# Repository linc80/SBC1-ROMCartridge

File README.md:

# SBC1-ROMCartridge
Contains the L80RomCartridge and L80RomCart-Adapter, needed to use the ROMSLOT header on a LiNC80 SBC1

The current version references libraries not included in the repository. There is a current TODO to change this over to using library files in the working project path, and verify compatibility with KiCad 5.

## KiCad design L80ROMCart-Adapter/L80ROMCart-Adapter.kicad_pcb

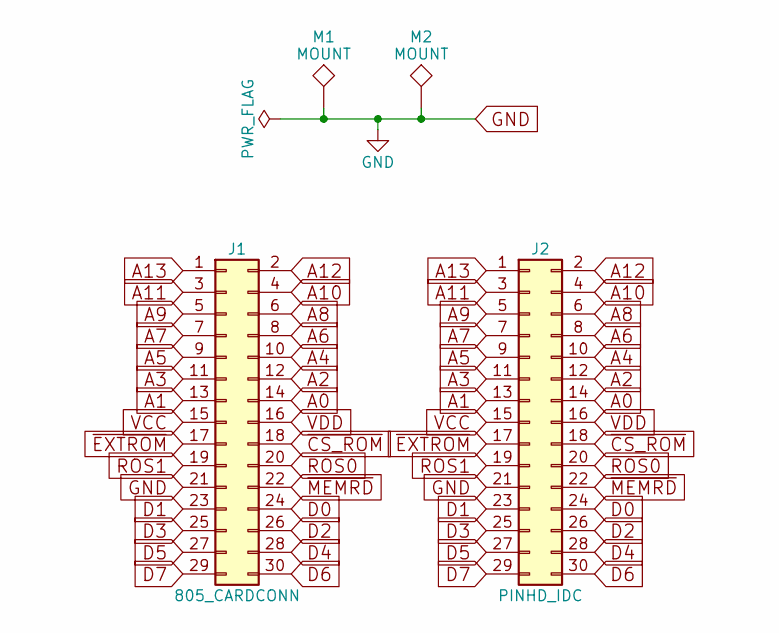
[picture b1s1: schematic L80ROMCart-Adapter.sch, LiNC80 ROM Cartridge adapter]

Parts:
J1: 805_CARDCONN; 805-connector-30pin
J2: PINHD_IDC; Pin_Header_Straight_2x15_Pitch2.54mm
M1, M2: MOUNT; MountingHole_3.5mm_Pad

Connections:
A0: J1.14, J2.14
A1: J1.13, J2.13
A2: J1.12, J2.12
A3: J1.11, J2.11
A4: J1.10, J2.10
A5: J1.9, J2.9
A6: J1.8, J2.8
A7: J1.7, J2.7
A8: J1.6, J2.6
A9: J1.5, J2.5
A10: J1.4, J2.4
A11: J1.3, J2.3
A12: J1.2, J2.2
A13: J1.1, J2.1
D0: J1.24, J2.24
D1: J1.23, J2.23
D2: J1.26, J2.26
D3: J1.25, J2.25
D4: J1.28, J2.28
D5: J1.27, J2.27
D6: J1.30, J2.30
D7: J1.29, J2.29
GND: J1.21, J2.21, M1.1, M2.1
ROS0: J1.20, J2.20
ROS1: J1.19, J2.19
VCC: J1.15, J2.15
VDD: J1.16, J2.16
~CS_ROM: J1.18, J2.18
~EXTROM: J1.17, J2.17
~MEMRD: J1.22, J2.22

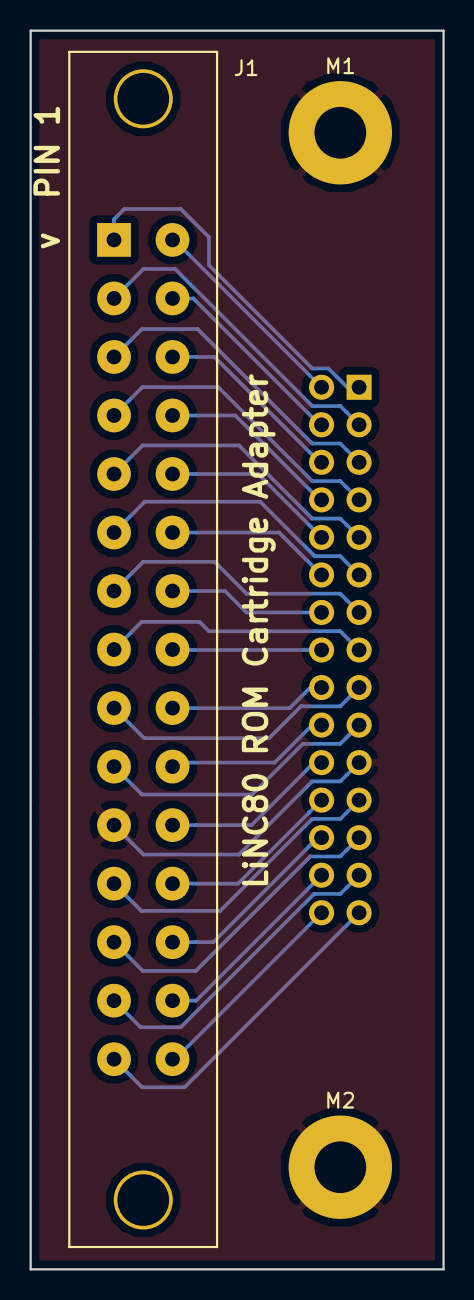
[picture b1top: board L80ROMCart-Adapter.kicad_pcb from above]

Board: 2 copper layers, 27.9 x 83.8 mm, 4 parts (1 on the bottom side), 30 nets.

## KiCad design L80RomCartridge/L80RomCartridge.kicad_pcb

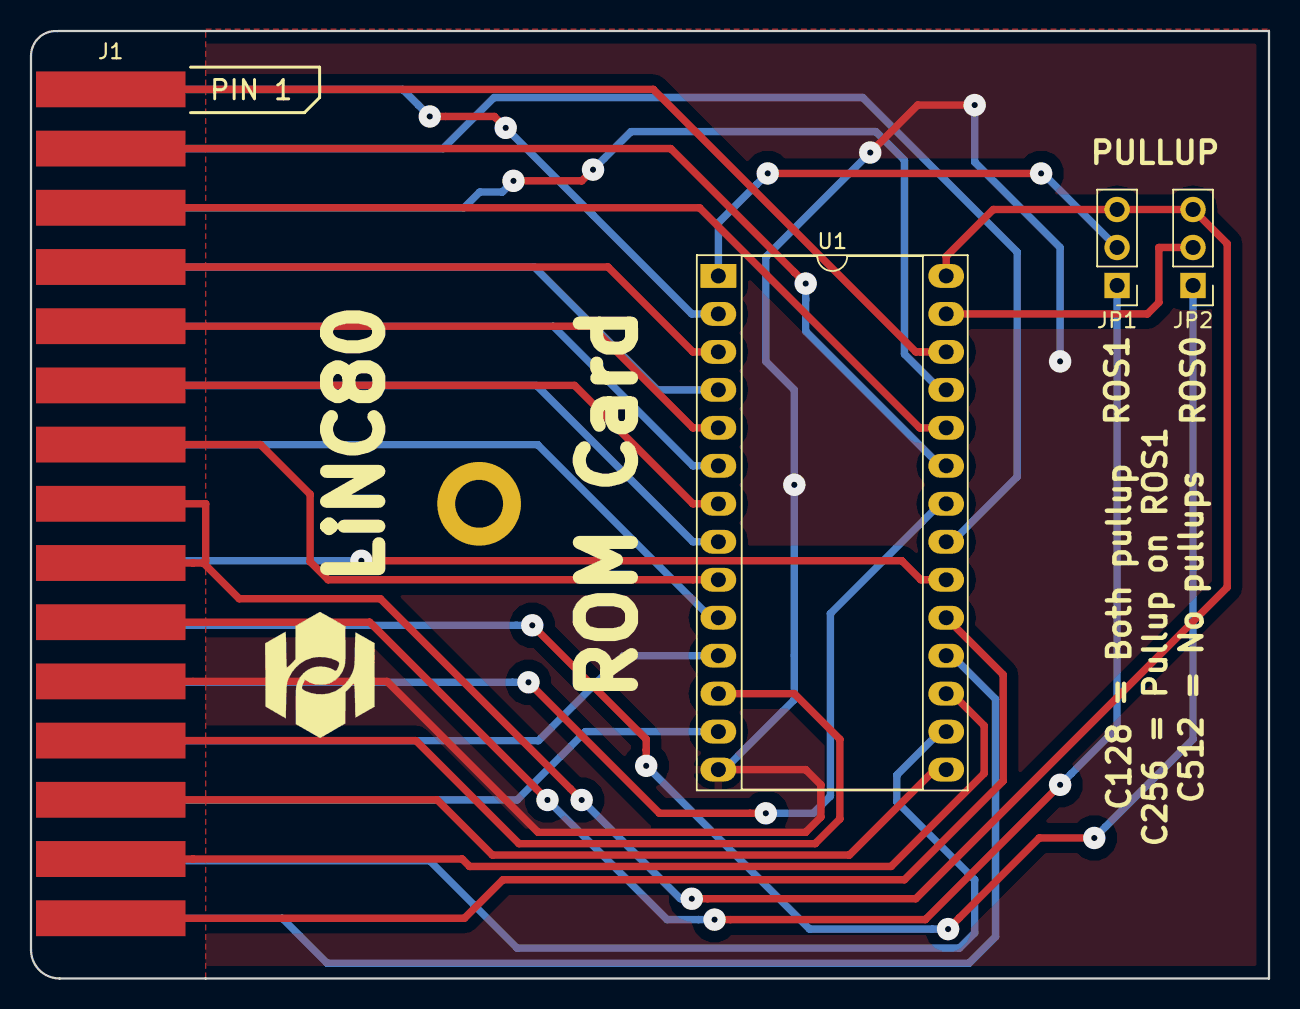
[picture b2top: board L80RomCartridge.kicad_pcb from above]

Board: 2 copper layers, 82.8 x 63.4 mm, 4 parts (0 on the bottom side), 30 nets.

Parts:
J1: Conn_02x15_Odd_Even; CardEdge-30pin-3.96p_OddEven
JP1, JP2: Jumper_NC_Dual; Pin_Header_Straight_1x03_Pitch2.54mm
U1: 27C512; DIP-28_W15.24mm_Socket_LongPads

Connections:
A0: J1.14, U1.10
A1: J1.13, U1.9
A2: J1.12, U1.8
A3: J1.11, U1.7
A4: J1.10, U1.6
A5: J1.9, U1.5
A6: J1.8, U1.4
A7: J1.7, U1.3
A8: J1.6, U1.25
A9: J1.5, U1.24
A10: J1.4, U1.21
A11: J1.3, U1.23
A12: J1.2, U1.2
A13: J1.1, U1.26
D0: J1.24, U1.11
D1: J1.23, U1.12
D2: J1.26, U1.13
D3: J1.25, U1.15
D4: J1.28, U1.16
D5: J1.27, U1.17
D6: J1.30, U1.18
D7: J1.29, U1.19
GND: J1.21, U1.14
unnamed: JP1.2, U1.1
unnamed: JP2.2, U1.27
ROS0: J1.20, JP2.1
ROS1: J1.19, JP1.1
VCC: J1.15, J1.17, JP1.3, JP2.3, U1.28
~CS_ROM: J1.18, U1.20
~MEMRD: J1.22, U1.22

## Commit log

2018-08-18 Starting with the .gitignore
2018-08-18 Current version of the ROM Card
2018-08-18 Current version of the Cartridge adapter (805-to-IDC)
2018-08-18 Added note about current issues to README.md
2018-08-18 Added Cache Libraries
